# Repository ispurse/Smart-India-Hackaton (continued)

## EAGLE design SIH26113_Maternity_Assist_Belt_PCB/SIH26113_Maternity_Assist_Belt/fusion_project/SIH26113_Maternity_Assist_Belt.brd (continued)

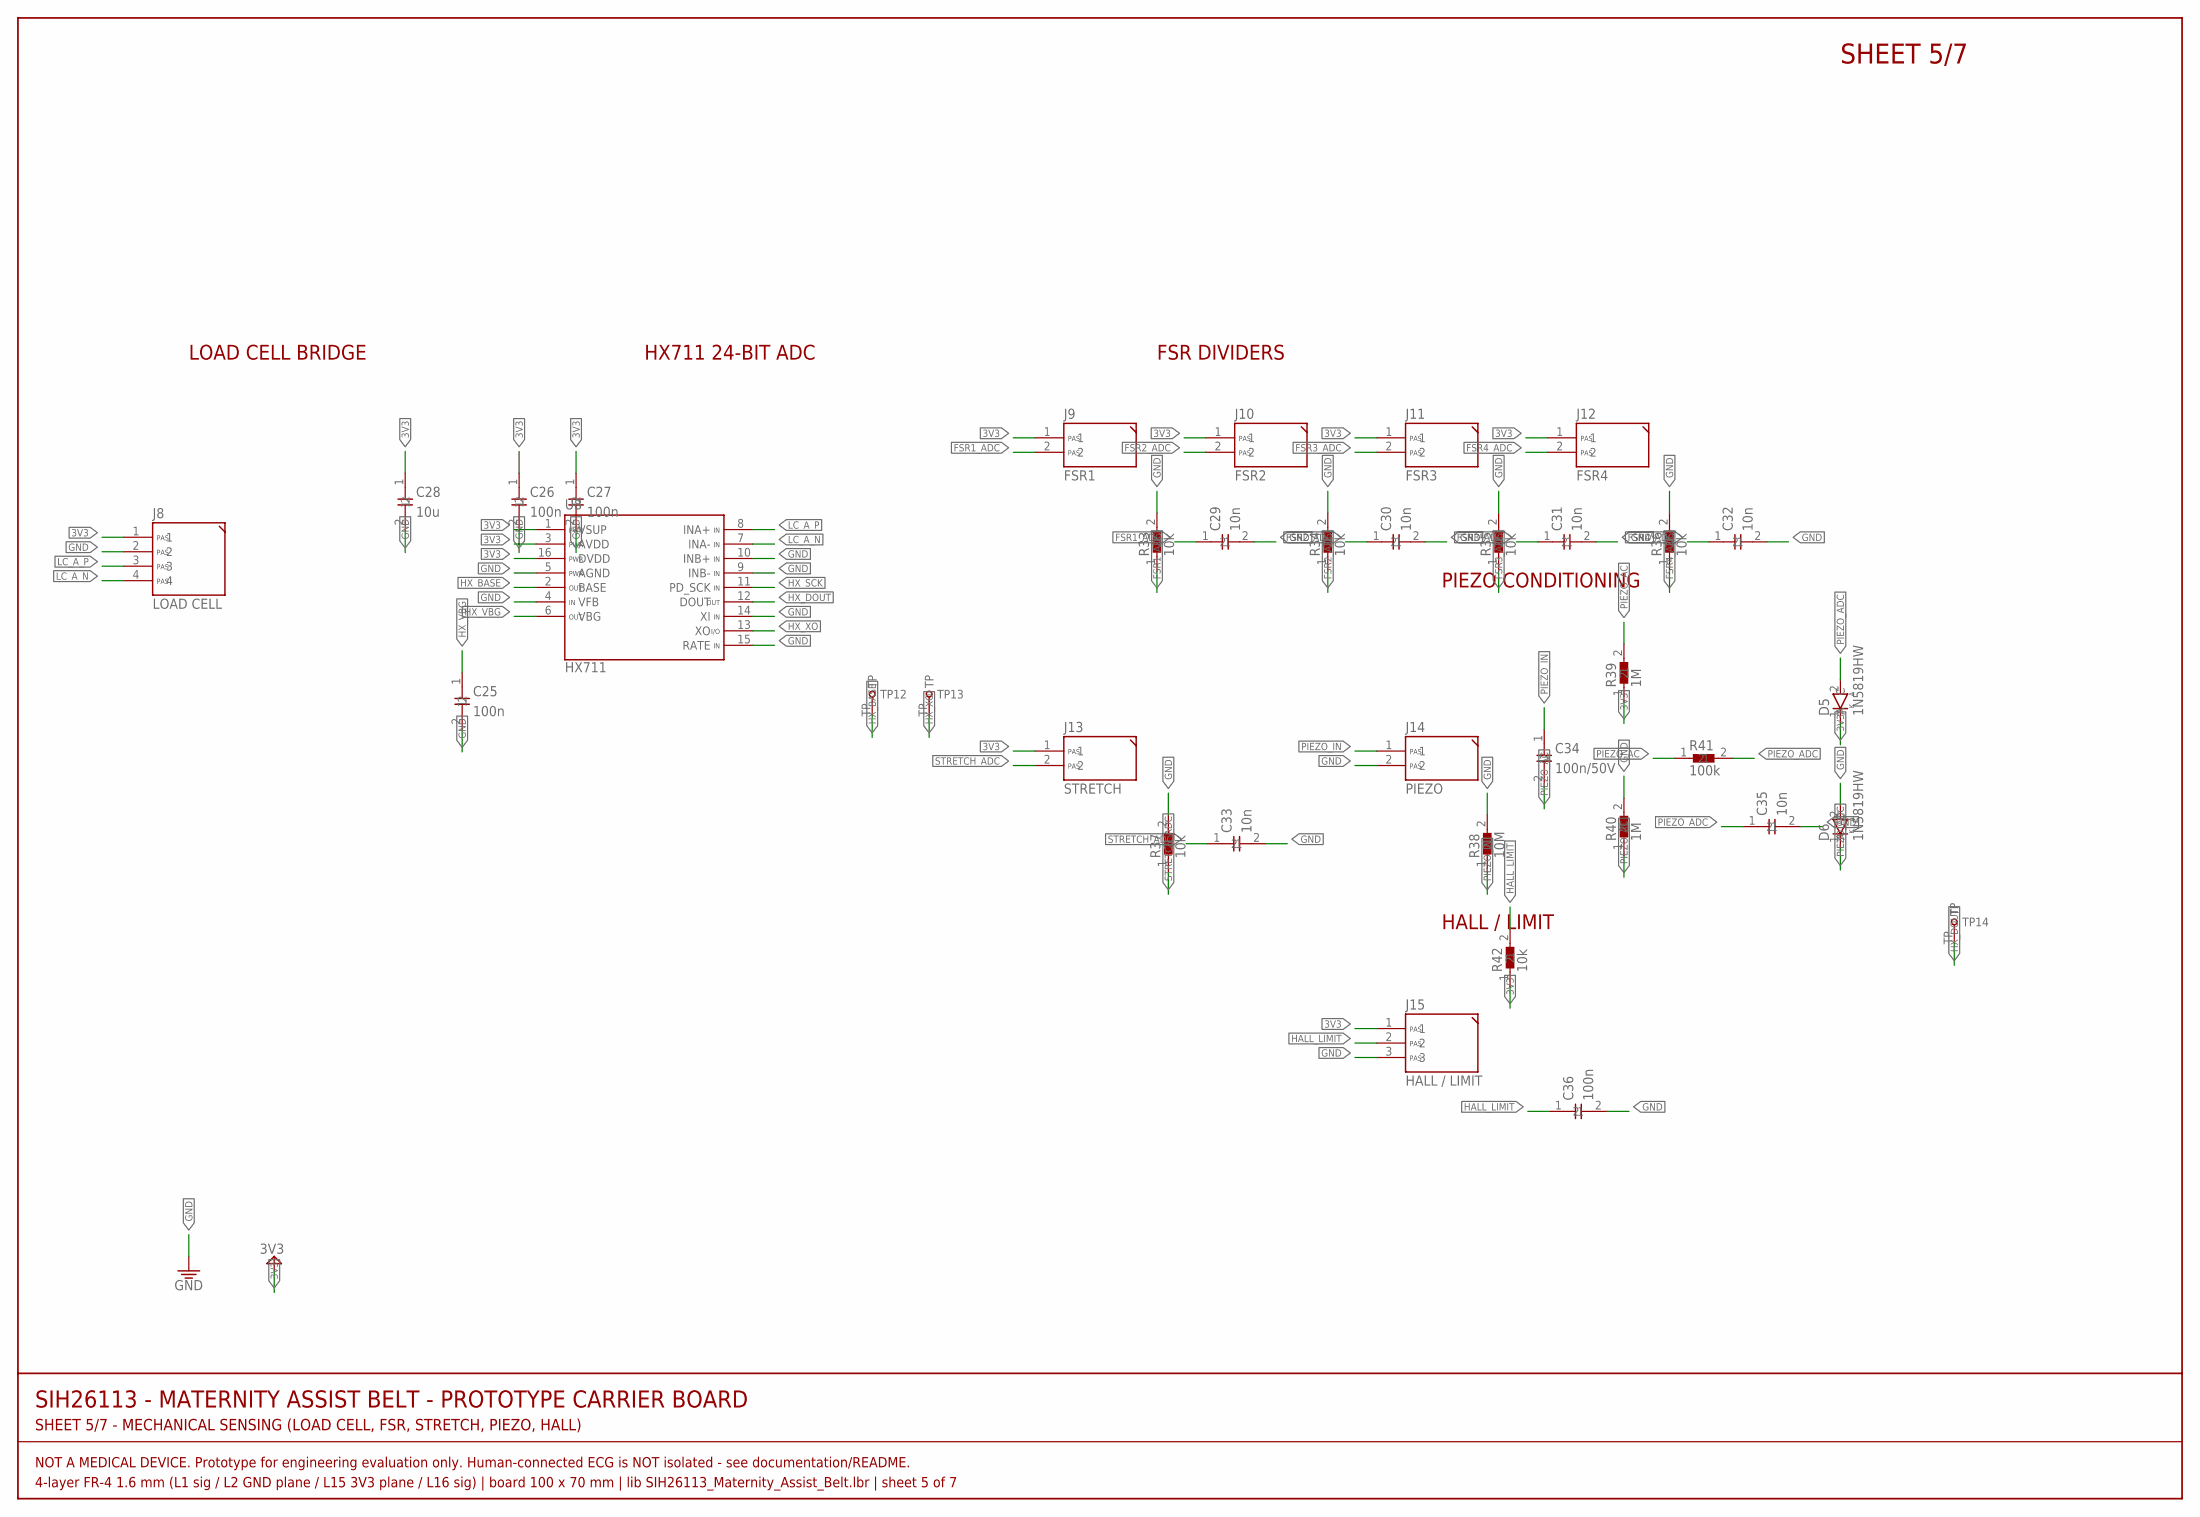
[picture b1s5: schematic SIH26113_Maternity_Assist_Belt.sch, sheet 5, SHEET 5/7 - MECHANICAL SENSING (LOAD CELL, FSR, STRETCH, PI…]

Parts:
C25, C26, C27, C36: 100n; C0805
C28: 10u; C0805
C29, C30, C31, C32, C33, C35: 10n; C0805
C34: 100n/50V; C0805
D5, D6: 1N5819HW; SOD-123
J8: LOAD CELL; JST-PH-4
J9: FSR1; HDR-1X2
J10: FSR2; HDR-1X2
J11: FSR3; HDR-1X2
J12: FSR4; HDR-1X2
J13: STRETCH; HDR-1X2
J14: PIEZO; HDR-1X2
J15: HALL / LIMIT; HDR-1X3
R33, R34, R35, R36, R37, R42: 10k; R0805
R38: 10M; R0805
R39, R40: 1M; R0805
R41: 100k; R0805
TP12: HX_BASE; TESTPOINT-1.5
TP13: HX_XO; TESTPOINT-1.5
TP14: HX_DOUT; TESTPOINT-1.5
U8: HX711; SOP-16-N

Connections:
3V3: C26.1, C27.1, C28.1, D5.1 (C), J8.1, J9.1, J10.1, J11.1, J12.1, J13.1, J15.1, R39.1, R42.1, U8.1 (VSUP), U8.3 (AVDD), U8.16 (DVDD); also elsewhere on the board
FSR1_ADC: C29.1, J9.2, R33.1; also elsewhere on the board
FSR2_ADC: C30.1, J10.2, R34.1; also elsewhere on the board
FSR3_ADC: C31.1, J11.2, R35.1; also elsewhere on the board
FSR4_ADC: C32.1, J12.2, R36.1; also elsewhere on the board
GND: C25.2, C26.2, C27.2, C28.2, C29.2, C30.2, C31.2, C32.2, C33.2, C35.2, C36.2, D6.2 (A), J8.2, J14.2, J15.3, R33.2, R34.2, R35.2, R36.2, R37.2, R38.2, R40.2, U8.4 (VFB), U8.5 (AGND), U8.9 (INB-), U8.10 (INB+), U8.14 (XI), U8.15 (RATE); also elsewhere on the board
HALL_LIMIT: C36.1, J15.2, R42.2; also elsewhere on the board
HX_BASE: TP12.TP, U8.2 (BASE)
HX_DOUT: TP14.TP, U8.12 (DOUT); also elsewhere on the board
HX_SCK: U8.11 (PD_SCK); also elsewhere on the board
HX_VBG: C25.1, U8.6 (VBG)
HX_XO: TP13.TP, U8.13 (XO)
LC_A_N: J8.4, U8.7 (INA-)
LC_A_P: J8.3, U8.8 (INA+)
PIEZO_AC: C34.2, R39.2, R40.1, R41.1
PIEZO_ADC: C35.1, D5.2 (A), D6.1 (C), R41.2; also elsewhere on the board
PIEZO_IN: C34.1, J14.1, R38.1
STRETCH_ADC: C33.1, J13.2, R37.1; also elsewhere on the board

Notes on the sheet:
SIH26113 - MATERNITY ASSIST BELT - PROTOTYPE CARRIER BOARD
SHEET 5/7 - MECHANICAL SENSING (LOAD CELL, FSR, STRETCH, PIEZO, HALL)
NOT A MEDICAL DEVICE. Prototype for engineering evaluation only. Human-connected ECG is NOT isolated - see documentation/README.
4-layer FR-4 1.6 mm (L1 sig / L2 GND plane / L15 3V3 plane / L16 sig) | board 100 x 70 mm | lib SIH26113_Maternity_Assist_Belt.lbr | sheet 5 of 7
SHEET 5/7
LOAD CELL BRIDGE
HX711 24-BIT ADC
FSR DIVIDERS
PIEZO CONDITIONING
HALL / LIMIT

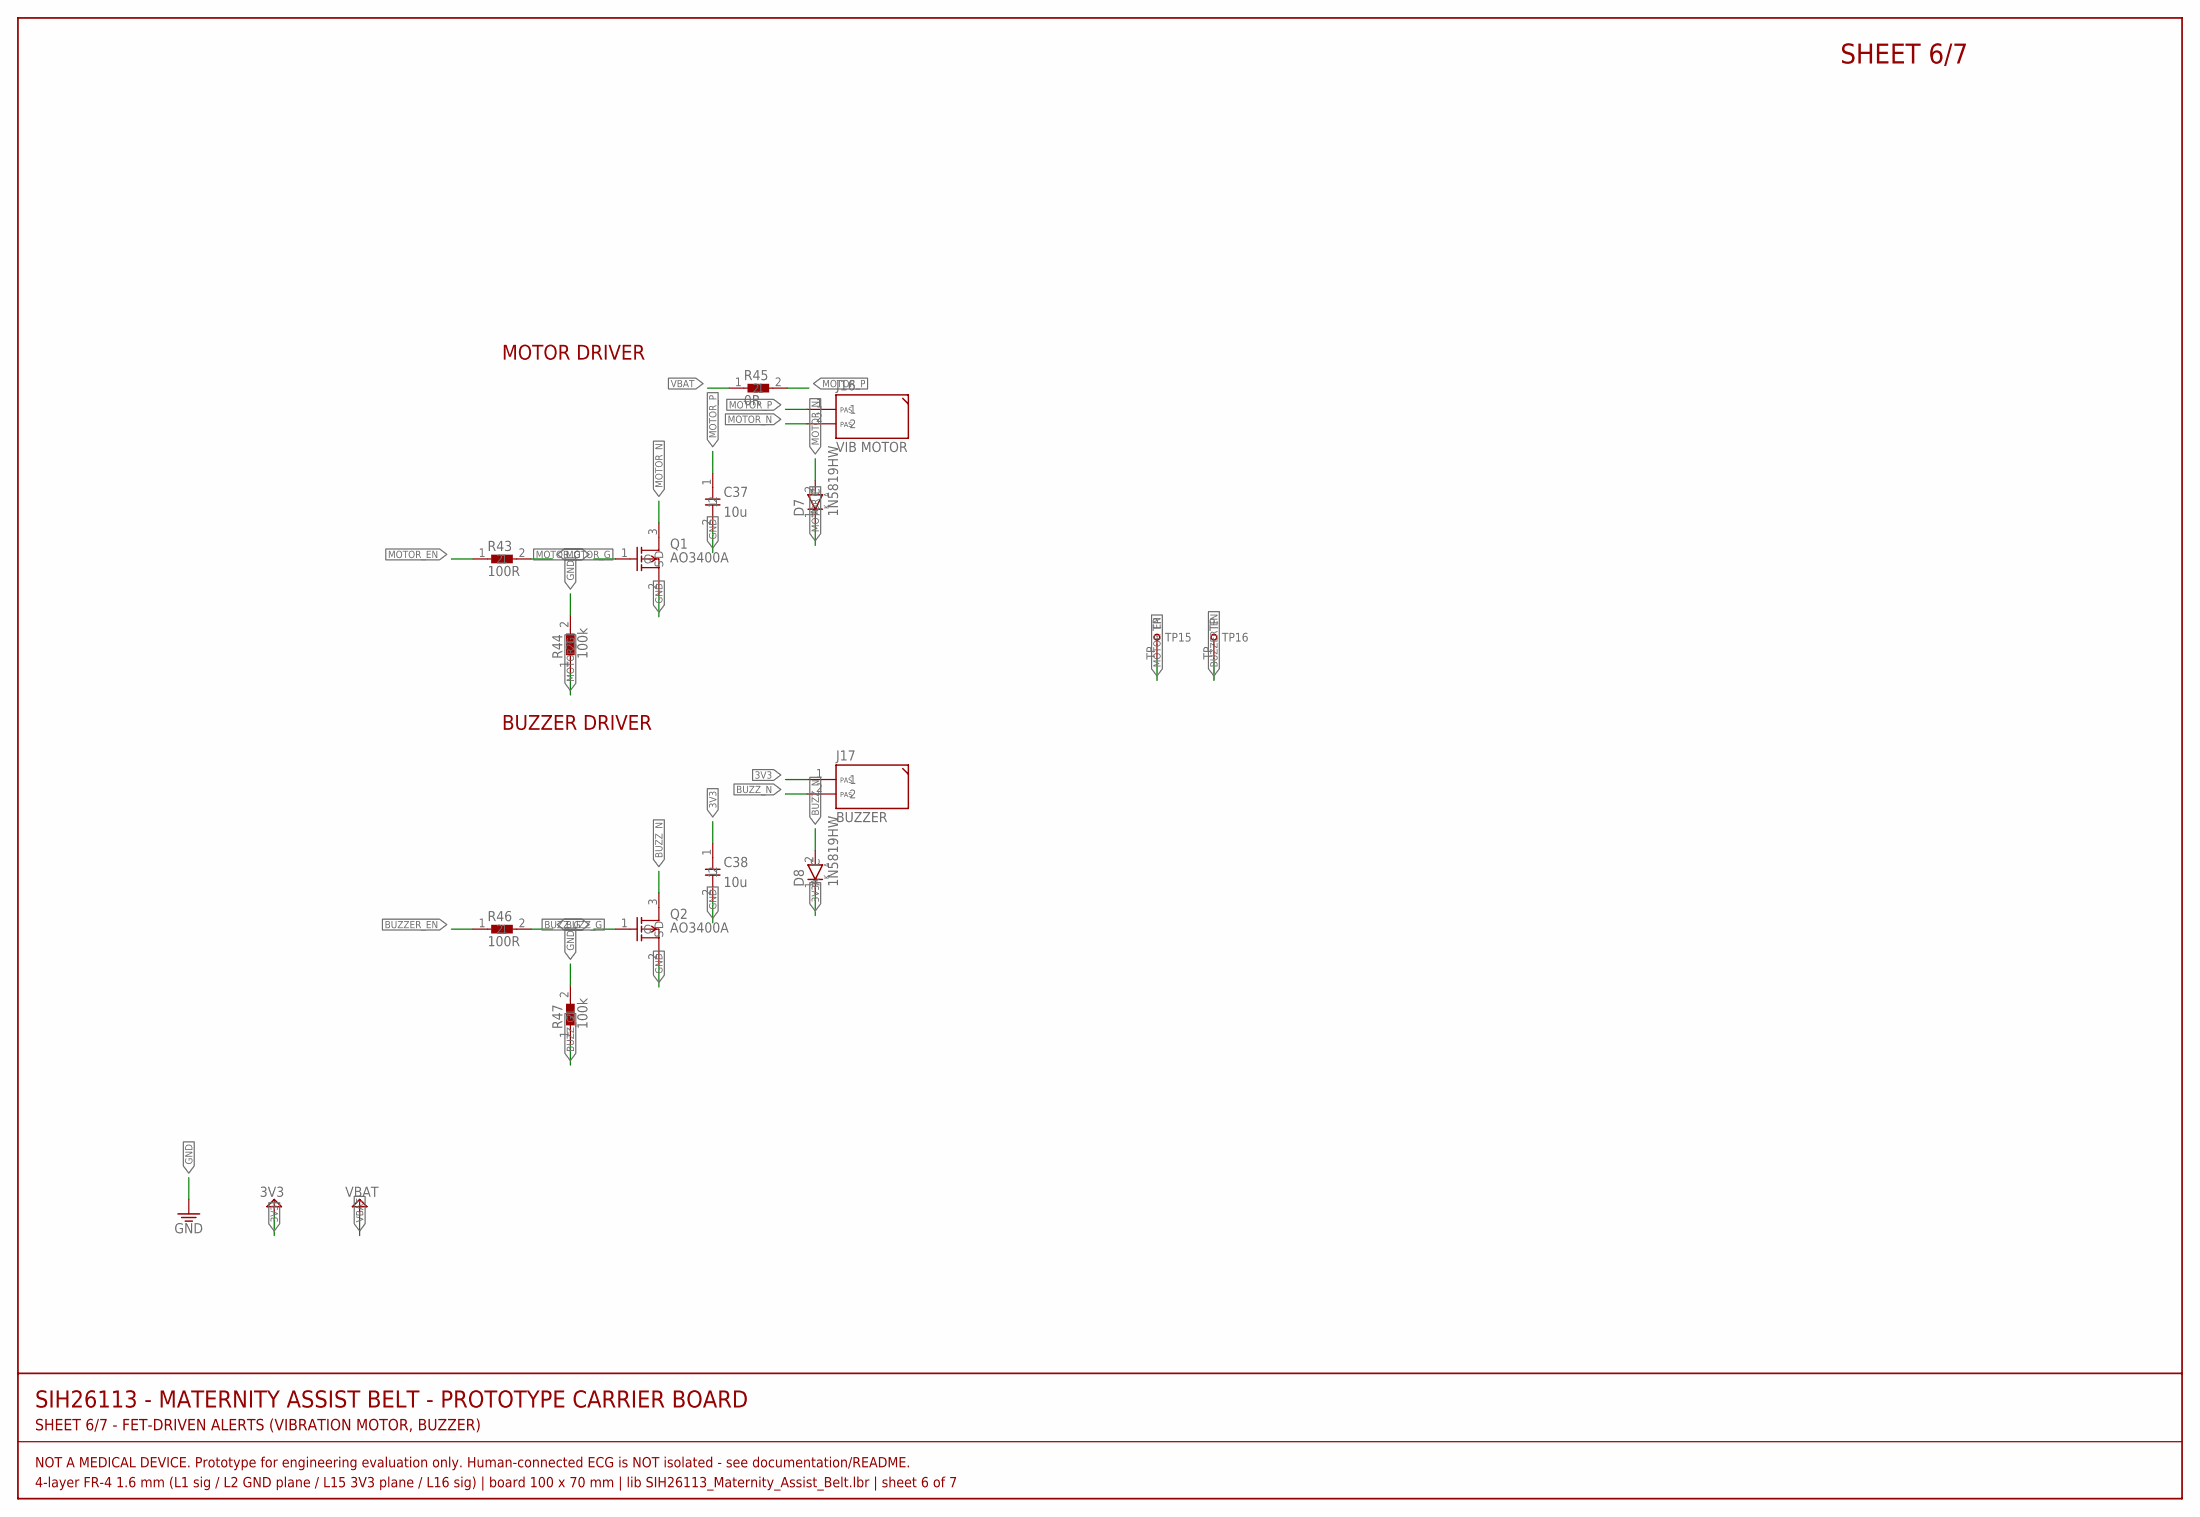
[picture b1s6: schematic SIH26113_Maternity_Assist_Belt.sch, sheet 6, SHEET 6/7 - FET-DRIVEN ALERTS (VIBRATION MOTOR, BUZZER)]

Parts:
C37, C38: 10u; C0805
D7, D8: 1N5819HW; SOD-123
J16: VIB MOTOR; HDR-1X2
J17: BUZZER; HDR-1X2
Q1, Q2: AO3400A; SOT-23-3
R43, R46: 100R; R0805
R44, R47: 100k; R0805
R45: 0R; R0805
TP15: MOTOR_EN; TESTPOINT-1.5
TP16: BUZZER_EN; TESTPOINT-1.5

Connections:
3V3: C38.1, D8.1 (C), J17.1; also elsewhere on the board
BUZZER_EN: R46.1, TP16.TP; also elsewhere on the board
BUZZ_G: Q2.1 (G), R46.2, R47.1
BUZZ_N: D8.2 (A), J17.2, Q2.3 (D)
GND: C37.2, C38.2, Q1.2 (S), Q2.2 (S), R44.2, R47.2; also elsewhere on the board
MOTOR_EN: R43.1, TP15.TP; also elsewhere on the board
MOTOR_G: Q1.1 (G), R43.2, R44.1
MOTOR_N: D7.2 (A), J16.2, Q1.3 (D)
MOTOR_P: C37.1, D7.1 (C), J16.1, R45.2
VBAT: R45.1; also elsewhere on the board

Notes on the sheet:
SIH26113 - MATERNITY ASSIST BELT - PROTOTYPE CARRIER BOARD
SHEET 6/7 - FET-DRIVEN ALERTS (VIBRATION MOTOR, BUZZER)
NOT A MEDICAL DEVICE. Prototype for engineering evaluation only. Human-connected ECG is NOT isolated - see documentation/README.
4-layer FR-4 1.6 mm (L1 sig / L2 GND plane / L15 3V3 plane / L16 sig) | board 100 x 70 mm | lib SIH26113_Maternity_Assist_Belt.lbr | sheet 6 of 7
SHEET 6/7
MOTOR DRIVER
BUZZER DRIVER

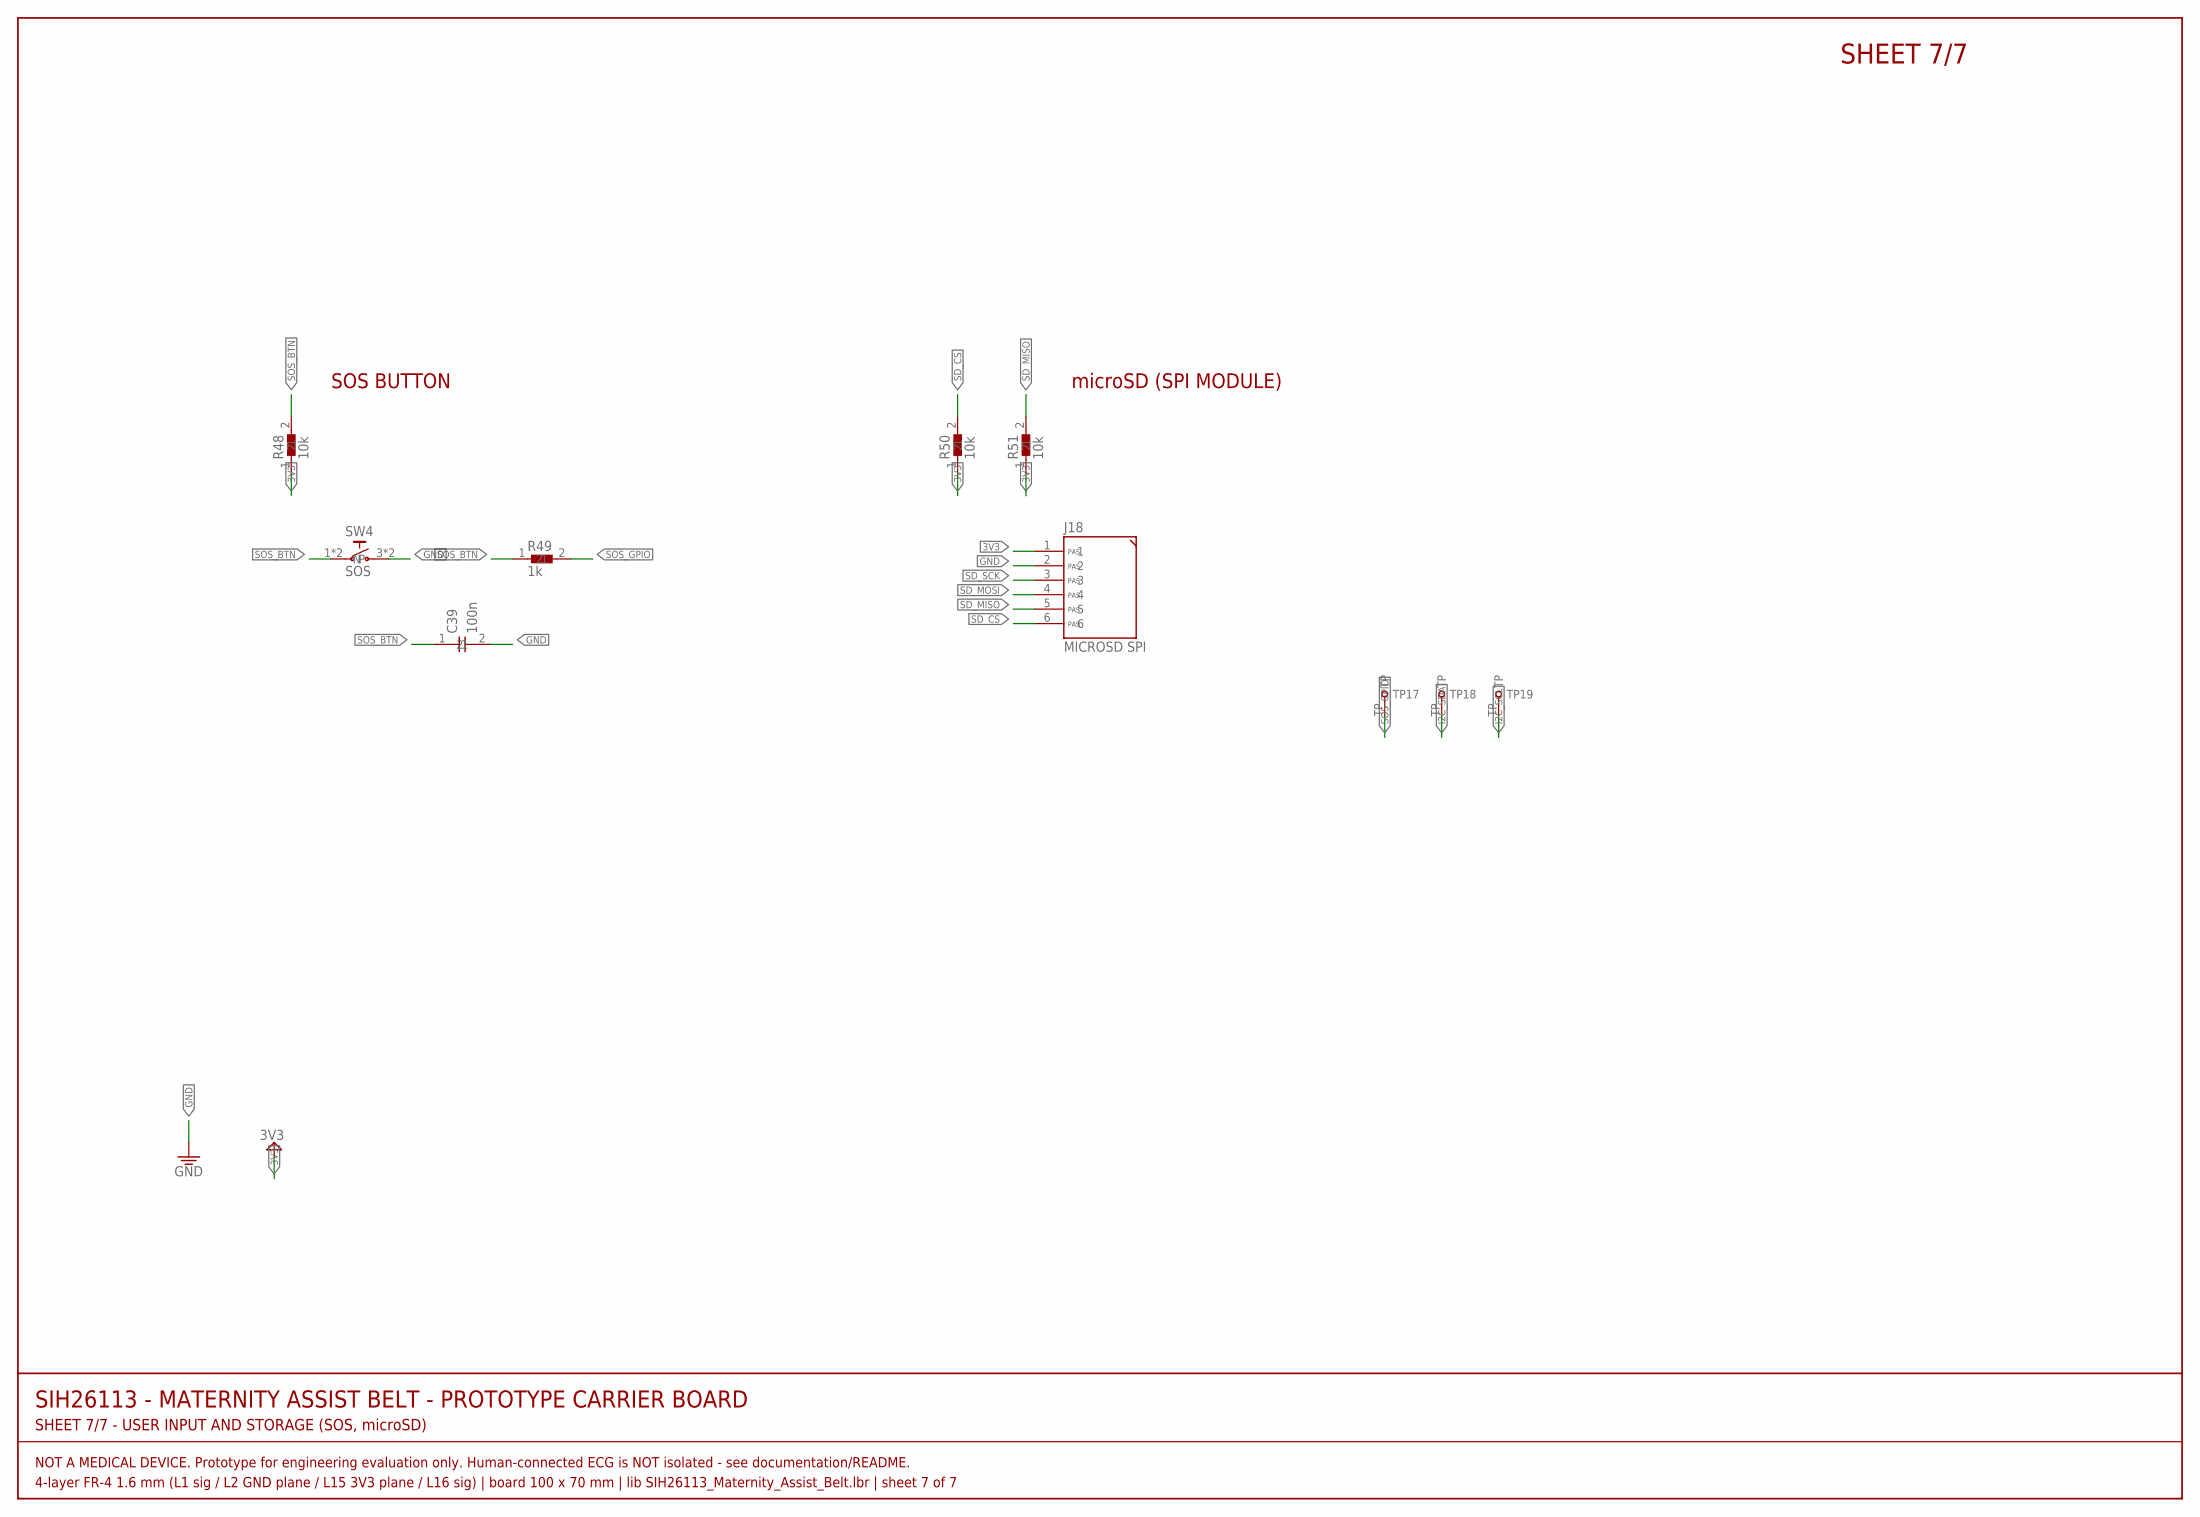
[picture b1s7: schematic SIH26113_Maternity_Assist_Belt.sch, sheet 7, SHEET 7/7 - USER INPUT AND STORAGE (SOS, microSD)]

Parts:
C39: 100n; C0805
J18: MICROSD SPI; HDR-1X6
R48, R50, R51: 10k; R0805
R49: 1k; R0805
SW4: SOS; TACT-6X6-THT
TP17: SOS_GPIO; TESTPOINT-1.5
TP18: I2C_SDA; TESTPOINT-1.5
TP19: I2C_SCL; TESTPOINT-1.5

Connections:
3V3: J18.1, R48.1, R50.1, R51.1; also elsewhere on the board
GND: C39.2, J18.2, SW4.3 (N), SW4.4 (N); also elsewhere on the board
I2C_SCL: TP19.TP; also elsewhere on the board
I2C_SDA: TP18.TP; also elsewhere on the board
SD_CS: J18.6, R50.2; also elsewhere on the board
SD_MISO: J18.5, R51.2; also elsewhere on the board
SD_MOSI: J18.4; also elsewhere on the board
SD_SCK: J18.3; also elsewhere on the board
SOS_BTN: C39.1, R48.2, R49.1, SW4.1, SW4.2
SOS_GPIO: R49.2, TP17.TP; also elsewhere on the board

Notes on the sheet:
SIH26113 - MATERNITY ASSIST BELT - PROTOTYPE CARRIER BOARD
SHEET 7/7 - USER INPUT AND STORAGE (SOS, microSD)
NOT A MEDICAL DEVICE. Prototype for engineering evaluation only. Human-connected ECG is NOT isolated - see documentation/README.
4-layer FR-4 1.6 mm (L1 sig / L2 GND plane / L15 3V3 plane / L16 sig) | board 100 x 70 mm | lib SIH26113_Maternity_Assist_Belt.lbr | sheet 7 of 7
SHEET 7/7
SOS BUTTON
microSD (SPI MODULE)

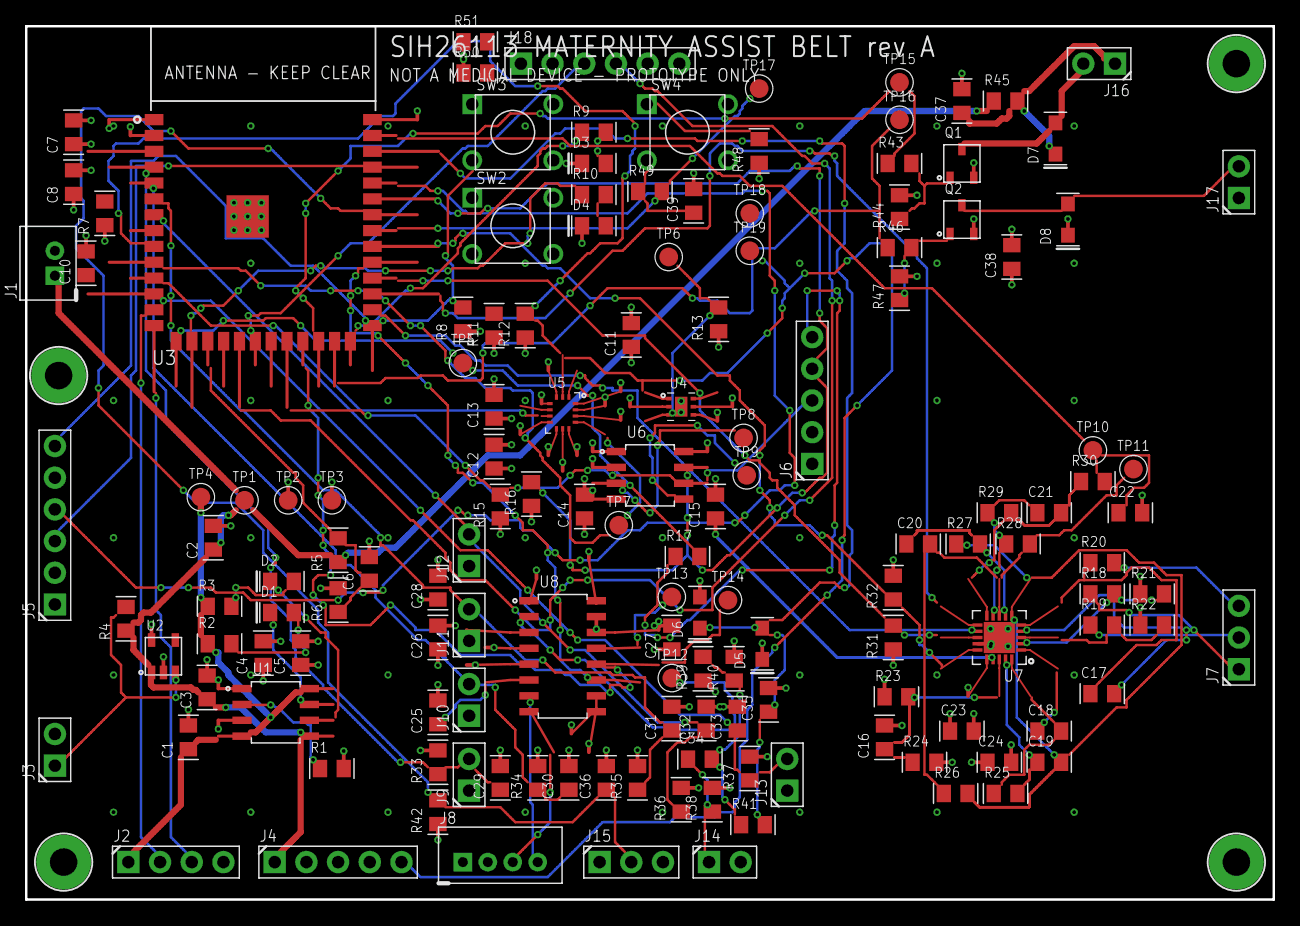
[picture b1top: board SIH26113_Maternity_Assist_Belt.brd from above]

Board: 4 copper layers, 100.0 x 70.0 mm, 150 parts (0 on the bottom side), 82 nets.

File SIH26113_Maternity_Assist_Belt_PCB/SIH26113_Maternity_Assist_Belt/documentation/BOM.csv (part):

Reference,Qty,Value,Manufacturer,MPN,Description,Package,Supplier,Supplier PN,Lifecycle,Library device,Notes
C1 C2 C3 C4 C28 C37 C38,7,10u,,,"Chip capacitor, 0805 (2012 metric)",C0805,,,,C-0805,VBUS input bulk
C10 C15 C24,3,1u,,,"Chip capacitor, 0805 (2012 metric)",C0805,,,,C-0805,EN RC delay (power-on reset)
C17,1,1n,,,"Chip capacitor, 0805 (2012 metric)",C0805,,,,C-0805,RLD integrator (RLDFB to RLD)
C18 C19,2,220n,,,"Chip capacitor, 0805 (2012 metric)",C0805,,,,C-0805,HPF pole 1 cap (HPDRIVE to HPSENSE)
C20,1,8n2,,,"Chip capacitor, 0805 (2012 metric)",C0805,,,,C-0805,LPF input cap -> ~41 Hz pole
C21,1,3n9,,,"Chip capacitor, 0805 (2012 metric)",C0805,,,,C-0805,Feedback cap -> ~41 Hz pole (2nd LPF pole)
C22 C29 C30 C31 C32 C33 C35,7,10n,,,"Chip capacitor, 0805 (2012 metric)",C0805,,,,C-0805,ADC input reservoir
C34,1,100n/50V,,,"Chip capacitor, 0805 (2012 metric)",C0805,,,,C-0805,Piezo AC coupling (must withstand the film's open-circuit transient)
C5 C6 C7 C11 C12 C13 C14 C16 C23 C25 C26 C27 C36 C39,14,100n,,,"Chip capacitor, 0805 (2012 metric)",C0805,,,,C-0805,LDO output HF bypass
C8,1,22u,,,"Chip capacitor, 0805 (2012 metric)",C0805,,,,C-0805,ESP32 3V3 bulk (Wi-Fi TX current burst)
D1 D4,2,RED,,,"Chip LED, 0805",LED0805,,,,LED-0805,Charging indicator
D2 D3,2,GRN,,,"Chip LED, 0805",LED0805,,,,LED-0805,Charge-complete indicator
D5 D6 D7 D8,4,1N5819HW,generic (Diodes/onsemi/MDD),1N5819HW,"Schottky/rectifier diode, SOD-123",SOD-123,,,,DIODE-SOD123,Piezo over-voltage clamp to 3V3
H1 H2 H3 H4,4,M2,,,"M2 plated mounting hole, GND-stitched",MOUNT-M2,,,,MOUNTHOLE-M2,"M2 mounting hole, GND-stitched"
J1,1,LI-PO 3.7V,JST,S2B-PH-K-S,JST PH 2,JST-PH-2,,,,JST-PH-2,Li-Po cell input (protected pack required)
J10,1,FSR2,-,FSR402 + 1x2 header,1x2 2,HDR-1X2,,,,HDR-1X2,Force-sensing resistor 2 (belt pressure)
J11,1,FSR3,-,FSR402 + 1x2 header,1x2 2,HDR-1X2,,,,HDR-1X2,Force-sensing resistor 3 (belt pressure)
J12,1,FSR4,-,FSR402 + 1x2 header,1x2 2,HDR-1X2,,,,HDR-1X2,Force-sensing resistor 4 (belt pressure)
J13,1,STRETCH,-,TBD - see REQUIRES_CONFIRMATION.md,1x2 2,HDR-1X2,,,,HDR-1X2,Abdominal stretch / extension sensor
J14,1,PIEZO,-,piezo film + 1x2 header,1x2 2,HDR-1X2,,,,HDR-1X2,Piezo film fetal-movement sensor
J15,1,HALL / LIMIT,-,generic 1x3 2.54mm header,1x3 2,HDR-1X3,,,,HDR-1X3,Hall or mechanical limit switch (rail travel)
J16,1,VIB MOTOR,-,generic 1x2 2.54mm header,1x2 2,HDR-1X2,,,,HDR-1X2,Vibration motor output
J17,1,BUZZER,-,generic 1x2 2.54mm header,1x2 2,HDR-1X2,,,,HDR-1X2,Magnetic or piezo buzzer output
J18,1,MICROSD SPI,-,generic microSD SPI breakout + 1x6 header,1x6 2,HDR-1X6,,,,HDR-1X6,microSD breakout module (SPI)
J2,1,USB / 5V IN,-,generic 1x4 2.54mm header,1x4 2,HDR-1X4,,,,HDR-1X4,5 V charge input + ESP32-S3 native USB D+/D-
J3,1,OFF SW,-,generic 1x2 2.54mm header,1x2 2,HDR-1X2,,,,HDR-1X2,External latching switch: closed = board OFF
J4,1,FUEL GAUGE,-,generic 1x5 2.54mm header,1x5 2,HDR-1X5,,,,HDR-1X5,"MAX17048 breakout header (I2C, addr 0x36)"
J5,1,UART PROG,-,generic 1x6 2.54mm header,1x6 2,HDR-1X6,,,,HDR-1X6,Fallback UART programming header
J6,1,AS5600 SIDE-B,-,generic 1x5 2.54mm header,1x5 2,HDR-1X5,,,,HDR-1X5,Second AS5600 (angle bus B + analog OUT)
J7,1,ECG ELECTRODES,-,generic 1x3 2.54mm header,1x3 2,HDR-1X3,,,,HDR-1X3,LA / RA / RL electrode leads
J8,1,LOAD CELL,JST,S4B-PH-K-S,JST PH 2,JST-PH-4,,,,JST-PH-4,"4-wire bridge: E+, E-, A+, A-"
J9,1,FSR1,-,FSR402 + 1x2 header,1x2 2,HDR-1X2,,,,HDR-1X2,Force-sensing resistor 1 (belt pressure)
Q1 Q2,2,AO3400A,Alpha & Omega Semiconductor,AO3400A,"N-channel logic-level MOSFET, SOT-23-3",SOT-23-3,,,,NMOS-SOT23,Low-side switch for the vibration motor
R1,1,2k4,,,"Chip resistor, 0805 (2012 metric)",R0805,,,,R-0805,TP4056 PROG: sets 500 mA charge current
R11 R12 R15 R16,4,4k7,,,"Chip resistor, 0805 (2012 metric)",R0805,,,,R-0805,I2C_SDA pull-up (bus A)
R17,1,0R DNP,,,"Chip resistor, 0805 (2012 metric)",R0805,,,,R-0805,Opt-in link: side-B AS5600 analog OUT -> IO3. Leave unpopulated unless the analog path is used (IO3 is a strapping pin).
R18 R19 R20,3,330k,,,"Chip resistor, 0805 (2012 metric)",R0805,,,,R-0805,LA patient-protection series R (Vs/10uA)
R2 R3 R9 R10 R30 R49,6,1k,,,"Chip resistor, 0805 (2012 metric)",R0805,,,,R-0805,CHRG LED current limit
R21 R22 R23 R24 R25 R38,6,10M,,,"Chip resistor, 0805 (2012 metric)",R0805,,,,R-0805,LA DC leads-off bias pull-up
R26 R29 R39 R40,4,1M,,,"Chip resistor, 0805 (2012 metric)",R0805,,,,R-0805,HPF pole 2 resistor (SW to REFOUT) -> 0.72 Hz
R4 R28 R31 R32 R41 R44 R47,7,100k,,,"Chip resistor, 0805 (2012 metric)",R0805,,,,R-0805,LDO EN pull-up to VBAT
R43 R46,2,100R,,,"Chip resistor, 0805 (2012 metric)",R0805,,,,R-0805,Motor gate series resistor (slew limit)
R45,1,0R,,,"Chip resistor, 0805 (2012 metric)",R0805,,,,R-0805,Motor ballast: populate only if the chosen motor is rated below 4.2 V
R5 R6 R27,3,470k,,,"Chip resistor, 0805 (2012 metric)",R0805,,,,R-0805,"VBAT sense divider, upper"
R7 R8 R13 R33 R34 R35 R36 R37 R42 R48 R50 R51,12,10k,,,"Chip resistor, 0805 (2012 metric)",R0805,,,,R-0805,EN pull-up
SW2,1,RESET,-,TL1105 family,6 x 6 mm through-hole tactile push-button,TACT-6X6-THT,,,,SW-TACT-6MM,Reset button (pulls EN low)
SW3,1,BOOT,-,TL1105 family,6 x 6 mm through-hole tactile push-button,TACT-6X6-THT,,,,SW-TACT-6MM,Boot button (pulls IO0 low)
SW4,1,SOS,-,TL1105 family,6 x 6 mm through-hole tactile push-button,TACT-6X6-THT,,,,SW-TACT-6MM,Manual emergency SOS button
TP1,1,VBAT,,,1,TESTPOINT-1.5,,,,TESTPOINT,Test point: VBAT
TP10,1,ECG_OUT,,,1,TESTPOINT-1.5,,,,TESTPOINT,Test point: conditioned ECG output
TP11,1,ECG_REF,,,1,TESTPOINT-1.5,,,,TESTPOINT,Test point: AD8232 REFOUT virtual ground
TP12,1,HX_BASE,,,1,TESTPOINT-1.5,,,,TESTPOINT,HX711 BASE (regulator unused: NC)
TP13,1,HX_XO,,,1,TESTPOINT-1.5,,,,TESTPOINT,HX711 XO (crystal unused: NC)
TP14,1,HX_DOUT,,,1,TESTPOINT-1.5,,,,TESTPOINT,Test point: HX711 serial data out
TP15,1,MOTOR_EN,,,1,TESTPOINT-1.5,,,,TESTPOINT,Test point: MOTOR_EN gate drive
TP16,1,BUZZER_EN,,,1,TESTPOINT-1.5,,,,TESTPOINT,Test point: BUZZER_EN gate drive
TP17,1,SOS_GPIO,,,1,TESTPOINT-1.5,,,,TESTPOINT,Test point: SOS GPIO
TP18,1,I2C_SDA,,,1,TESTPOINT-1.5,,,,TESTPOINT,Test point: sensor-bus SDA
TP19,1,I2C_SCL,,,1,TESTPOINT-1.5,,,,TESTPOINT,Test point: sensor-bus SCL
TP2,1,3V3,,,1,TESTPOINT-1.5,,,,TESTPOINT,Test point: 3V3
TP3,1,GND,,,1,TESTPOINT-1.5,,,,TESTPOINT,Test point: GND
TP4,1,VBUS,,,1,TESTPOINT-1.5,,,,TESTPOINT,Test point: VBUS
TP5,1,IO3,,,1,TESTPOINT-1.5,,,,TESTPOINT,Test point: IO3 spare / ANG2_OUT
TP6,1,TMP_ALERT,,,1,TESTPOINT-1.5,,,,TESTPOINT,Test point: TMP117 ALERT (not routed to a GPIO)
TP7,1,IMU_INT1,,,1,TESTPOINT-1.5,,,,TESTPOINT,Test point: IMU interrupt 1
TP8,1,AS_OUT,,,1,TESTPOINT-1.5,,,,TESTPOINT,"AS5600 analog/PWM OUT (unused, I2C is used)"
TP9,1,AS_PGO,,,1,TESTPOINT-1.5,,,,TESTPOINT,AS5600 PGO programming pin (internal pull-up)
U1,1,TP4056,NanJing Top Power,TP4056-42-SOP8-PP,"NanJing Top Power TP4056-42-SOP8-PP 1 A standalone linear Li-ion charger, 4",SOIC-8-N,,,,TP4056,"1 A linear Li-ion charger, 4.2 V float"
U2,1,AP2112K-3.3,,,Diodes AP2112K-3,SOT-23-5,,,,AP2112K-3.3,"600 mA LDO, 3.3 V fixed"
U3,1,ESP32-S3-WROOM-1-N8R2,Espressif Systems,ESP32-S3-WROOM-1-N8R2,Espressif ESP32-S3-WROOM-1-N8R2,ESP32-S3-WROOM-1,,,,ESP32-S3-WROOM-1,"Central MCU: Xtensa LX7 dual core, Wi-Fi + BLE 5, 8 MB flash, 2 MB PSRAM"
U4,1,TMP117,Texas Instruments,TMP117AIDRVR,"TI TMP117AIDRVR high-accuracy digital temperature sensor, WSON-6 (DRV)",WSON-6-DRV0006B,,,,TMP117,"Digital temperature sensor, I2C addr 0x48"
U5,1,LSM6DSOX,STMicroelectronics,LSM6DSOXTR,"ST LSM6DSOXTR 6-axis IMU (3-axis accel + 3-axis gyro), LGA-14L",LGA-14L-2.5X3.0,,,,LSM6DSOX,"6-axis IMU, I2C addr 0x6A"
U6,1,AS5600,ams-OSRAM,AS5600-ASOM,"ams-OSRAM AS5600-ASOM 12-bit contactless magnetic rotary position sensor, SOIC-8",SOIC-8-N,,,,AS5600,"12-bit magnetic angle sensor, I2C addr 0x36 (fixed)"
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
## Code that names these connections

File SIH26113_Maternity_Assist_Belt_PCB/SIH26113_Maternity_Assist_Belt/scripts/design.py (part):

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P("R10", "R-0805", "1k", "LED_ALERT current limit", 2, 210, 96, "R0", 38.5, 48.0, "R0")
P("D4", "LED-0805", "RED", "Alert LED (IO46)", 2, 224, 96, "R0", 41.5, 48.0, "R0")
P("TP5", "TESTPOINT", "IO3", "Test point: IO3 spare / ANG2_OUT", 2, 250, 80, "R0", 31.0, 33.0, "R0")
P("TP6", "TESTPOINT", "TMP_ALERT", "Test point: TMP117 ALERT (not routed to a GPIO)",
  2, 260, 80, "R0", 49.5, 41.5, "R0")
P("SUPPLY5", "SUPPLY-GND", "GND", "GND rail declaration", 2, 30, 60)
P("SUPPLY6", "SUPPLY-3V3", "3V3", "3V3 rail declaration", 2, 45, 60)
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  3, 68, 70, "R0", 49.0, 26.5, "R90")
P("TP8", "TESTPOINT", "AS_OUT", "AS5600 analog/PWM OUT (unused, I2C is used)",
  3, 140, 68, "R0", 50.5, 32.0)
P("TP9", "TESTPOINT", "AS_PGO", "AS5600 PGO programming pin (internal pull-up)",
  3, 150, 68, "R0", 50.5, 29.0)
P("J6", "HDR-1X5", "AS5600 SIDE-B", "Second AS5600 (angle bus B + analog OUT)",
  3, 200, 80, "R0", 52.0, 30.0, "R90",
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P("R50", "R-0805", "10k", "SD_CS pull-up (SD spec recommends 10k-100k)",
  7, 165, 185, "R90", 30.0, 53.5, "R0")
P("R51", "R-0805", "10k", "SD_MISO pull-up", 7, 177, 185, "R90", 30.0, 56.0, "R0")
P("TP17", "TESTPOINT", "SOS_GPIO", "Test point: SOS GPIO", 7, 240, 140, "R0", 52.0, 55.0, "R0")
P("TP18", "TESTPOINT", "I2C_SDA", "Test point: sensor-bus SDA", 7, 250, 140, "R0", 52.0, 45.0, "R0")
P("TP19", "TESTPOINT", "I2C_SCL", "Test point: sensor-bus SCL", 7, 260, 140, "R0", 52.0, 42.0, "R0")
P("SUPPLY16", "SUPPLY-GND", "GND", "GND rail declaration", 7, 30, 60)
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
# ---- User input / storage ----------------------------------------------
N("SOS_BTN", "SW4.P", "R48.2", "C39.1", "R49.1")
N("SOS_GPIO", "R49.2", "U3.IO40", "TP17.TP")
N("SD_SCK", "J18.3", "U3.IO12")
N("SD_MOSI", "J18.4", "U3.IO11")
N("SD_MISO", "J18.5", "U3.IO13", "R51.2")
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

GPIO_TABLE: list[Gpio] = [
    Gpio("IO0", "27", "BOOT strap / boot button", "ESP_IO0", "IO", True, "-", "-",
         "SW3, R8, J5.6",
         "Weak internal pull-up. Held low at reset = download mode."),
    Gpio("IO1", "39", "ECG analog output", "ECG_OUT", "ANALOG IN", False,
         "ADC1_CH0", "ADC1", "U7 via R30/C22",
         "ADC1 is the only ADC usable while the radio is on."),
    Gpio("IO2", "38", "Piezo (fetal movement)", "PIEZO_ADC", "ANALOG IN", False,
         "ADC1_CH1", "ADC1", "J14 chain, D5/D6 clamped", ""),
    Gpio("IO3", "15", "Spare / side-B AS5600 analog OUT", "IO3_SPARE", "ANALOG IN",
         True, "ADC1_CH2", "ADC1", "TP5, R17 (DNP)",
         "STRAPPING (JTAG source select). R17 left unpopulated by default."),
    Gpio("IO4", "4", "FSR1 (belt pressure)", "FSR1_ADC", "ANALOG IN", False,
         "ADC1_CH3", "ADC1", "J9/R33/C29", ""),
    Gpio("IO5", "5", "FSR2 (belt pressure)", "FSR2_ADC", "ANALOG IN", False,
         "ADC1_CH4", "ADC1", "J10/R34/C30", ""),
    Gpio("IO6", "6", "FSR3 (belt pressure)", "FSR3_ADC", "ANALOG IN", False,
         "ADC1_CH5", "ADC1", "J11/R35/C31", ""),
    Gpio("IO7", "7", "FSR4 (belt pressure)", "FSR4_ADC", "ANALOG IN", False,
         "ADC1_CH6", "ADC1", "J12/R36/C32", ""),
    Gpio("IO8", "12", "Stretch sensor", "STRETCH_ADC", "ANALOG IN", False,
         "ADC1_CH7", "ADC1", "J13/R37/C33", "R37 value is a placeholder."),
    Gpio("IO9", "17", "Battery voltage sense", "VBAT_SENSE", "ANALOG IN", False,
         "ADC1_CH8", "ADC1", "R5/R6/C6",
         "470k/470k halves VBAT; 4.2 V cell -> 2.10 V at the pin."),
    Gpio("IO10", "18", "microSD chip select", "SD_CS", "OUT", False,
         "ADC1_CH9 (unused)", "FSPICS0", "J18.6, R50", ""),
    Gpio("IO11", "19", "microSD MOSI", "SD_MOSI", "OUT", False, "ADC2", "FSPID",
         "J18.4", ""),
    Gpio("IO12", "20", "microSD SCK", "SD_SCK", "OUT", False, "ADC2", "FSPICLK",
         "J18.3", ""),
    Gpio("IO13", "21", "microSD MISO", "SD_MISO", "IN", False, "ADC2", "FSPIQ",
         "J18.5, R51", ""),
    Gpio("IO14", "22", "Angle-bus I2C SDA", "ANG_SDA", "IO", False, "ADC2",
         "I2C1", "U6, J6, R15", "Separate bus resolves the 0x36 clash."),
    Gpio("IO15", "8", "Sensor-bus I2C SDA", "I2C_SDA", "IO", False, "ADC2",
         "I2C0", "U4, U5, J4, R11", ""),
    Gpio("IO16", "9", "Sensor-bus I2C SCL", "I2C_SCL", "OUT", False, "ADC2",
         "I2C0", "U4, U5, J4, R12", ""),
    Gpio("IO17", "10", "IMU interrupt 1", "IMU_INT1", "IN", False, "ADC2", "GPIO",
         "U5.INT1", ""),
    Gpio("IO18", "11", "IMU interrupt 2", "IMU_INT2", "IN", False, "ADC2", "GPIO",
         "U5.INT2", ""),
    Gpio("IO19", "13", "USB D-", "USB_DM", "IO", False, "ADC2", "USB-Serial-JTAG",
         "J2.2", "Route as a 90 ohm differential pair with IO20."),
    Gpio("IO20", "14", "USB D+", "USB_DP", "IO", False, "ADC2", "USB-Serial-JTAG",
         "J2.3", ""),
    Gpio("IO21", "23", "HX711 serial data out", "HX_DOUT", "IN", False, "-",
         "GPIO", "U8.DOUT", ""),
    Gpio("IO35", "28", "ECG leads-off, + input", "ECG_LOD_P", "IN", False, "-",
         "GPIO", "U7.LOD+",
         "Free on -N8R2 only. Octal-PSRAM parts reserve IO35/36/37."),
    Gpio("IO36", "29", "ECG leads-off, - input", "ECG_LOD_N", "IN", False, "-",
         "GPIO", "U7.LOD-", "See IO35 note."),
    Gpio("IO37", "30", "ECG shutdown control", "ECG_SDN", "OUT", False, "-",
         "GPIO", "U7.SDN, R31", "R31 keeps the AFE enabled if the GPIO floats."),
    Gpio("IO38", "31", "HX711 clock / power-down", "HX_SCK", "OUT", False, "-",
         "GPIO", "U8.PD_SCK", ""),
    Gpio("IO39", "32", "ECG fast restore", "ECG_FR", "OUT", False, "-",
         "GPIO (was MTCK)", "U7.FR, R32",
         "Pin-JTAG is given up; debugging uses the built-in USB-Serial-JTAG."),
    Gpio("IO40", "33", "SOS button", "SOS_GPIO", "IN", False, "-",
         "GPIO (was MTDO)", "SW4 via R49", ""),
    Gpio("IO41", "34", "Hall / limit switch", "HALL_LIMIT", "IN", False, "-",
         "GPIO (was MTDI)", "J15, R42", ""),
    Gpio("IO42", "35", "Angle-bus I2C SCL", "ANG_SCL", "OUT", False, "-",
         "I2C1 (was MTMS)", "U6, J6, R16", ""),
    Gpio("TXD0", "37", "UART0 TX", "UART_TX", "OUT", False, "-", "UART0",
         "J5.3", "GPIO43."),
    Gpio("RXD0", "36", "UART0 RX", "UART_RX", "IN", False, "-", "UART0",
         "J5.4", "GPIO44."),
    Gpio("IO45", "26", "Status LED (green)", "LED_STATUS", "OUT", True, "-",
         "GPIO", "R9, D3",
         "STRAPPING (VDD_SPI). LED to GND keeps the strap at its default 0."),
    Gpio("IO46", "16", "Alert LED (red)", "LED_ALERT", "OUT", True, "-", "GPIO",
         "R10, D4",
         "STRAPPING (ROM print). LED to GND keeps the strap at its default 0."),
    Gpio("IO47", "24", "Vibration motor enable", "MOTOR_EN", "OUT", False, "-",
         "GPIO", "R43 -> Q1", ""),
    Gpio("IO48", "25", "Buzzer enable", "BUZZER_EN", "OUT", False, "-", "GPIO",
         "R46 -> Q2", ""),
    Gpio("EN", "3", "Chip enable / reset", "ESP_EN", "IN", True, "-", "-",
         "R7, C10, SW2, J5.5", "Must not be left floating."),
    Gpio("3V3", "2", "Module supply", "3V3", "POWER", False, "-", "-",
         "C7, C8", ""),
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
